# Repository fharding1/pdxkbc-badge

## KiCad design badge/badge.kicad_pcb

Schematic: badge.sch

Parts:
D1, D2, D3, D4, D5, D6: D; D_SOD123_axial
K1, K2, K3, K4, K5, K6: KEYSW; Mx_Alps_100
U1: ProMicro; SPARKFUN_PRO_MICRO

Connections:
/col0: K1.1, K2.1, K3.1, U1.5
/col1: K4.1, K5.1, K6.1, U1.10
/row0: D1.1 (K), D4.1 (K), U1.17
/row1: D2.1 (K), D5.1 (K), U1.13
/row2: D3.1 (K), D6.1 (K), U1.20
GND: U1.3, U1.4, U1.23
unnamed: D1.2 (A), K1.2
unnamed: D2.2 (A), K2.2
unnamed: D3.2 (A), K3.2
unnamed: D4.2 (A), K4.2
unnamed: D5.2 (A), K5.2
unnamed: D6.2 (A), K6.2

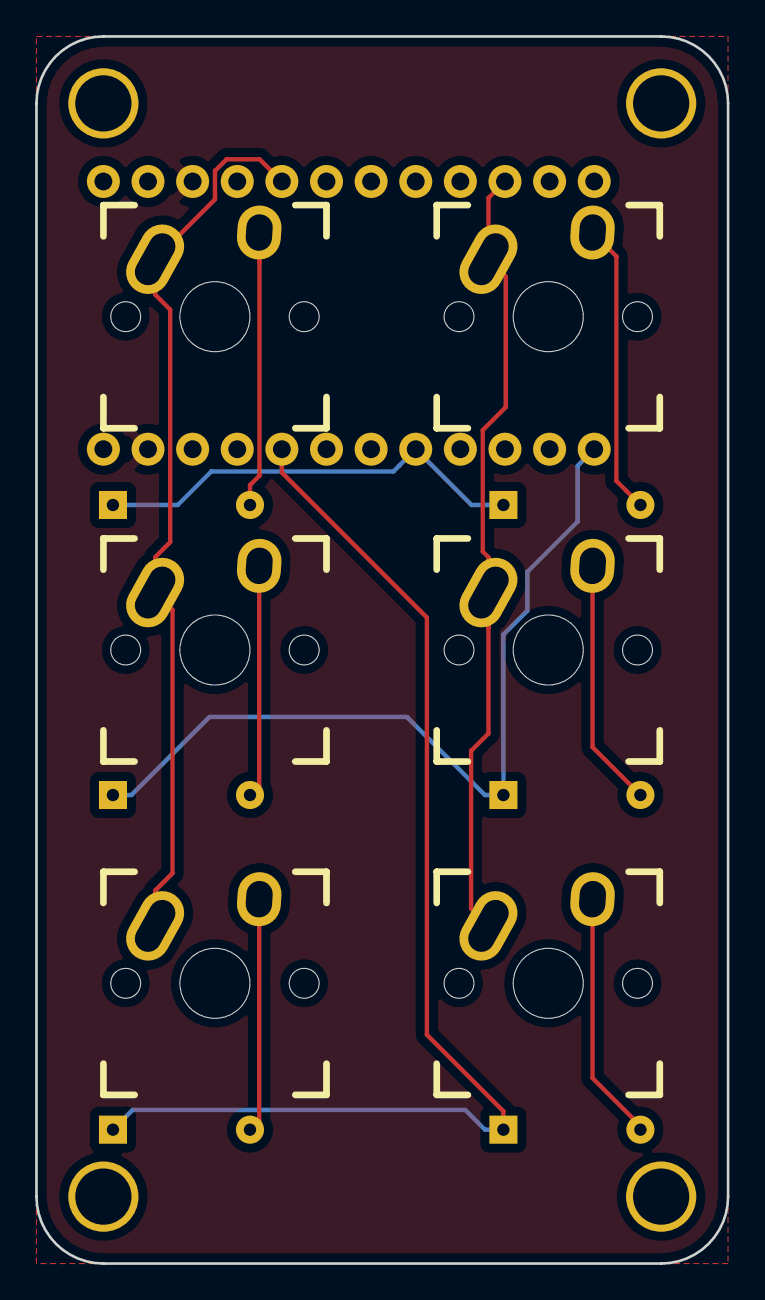
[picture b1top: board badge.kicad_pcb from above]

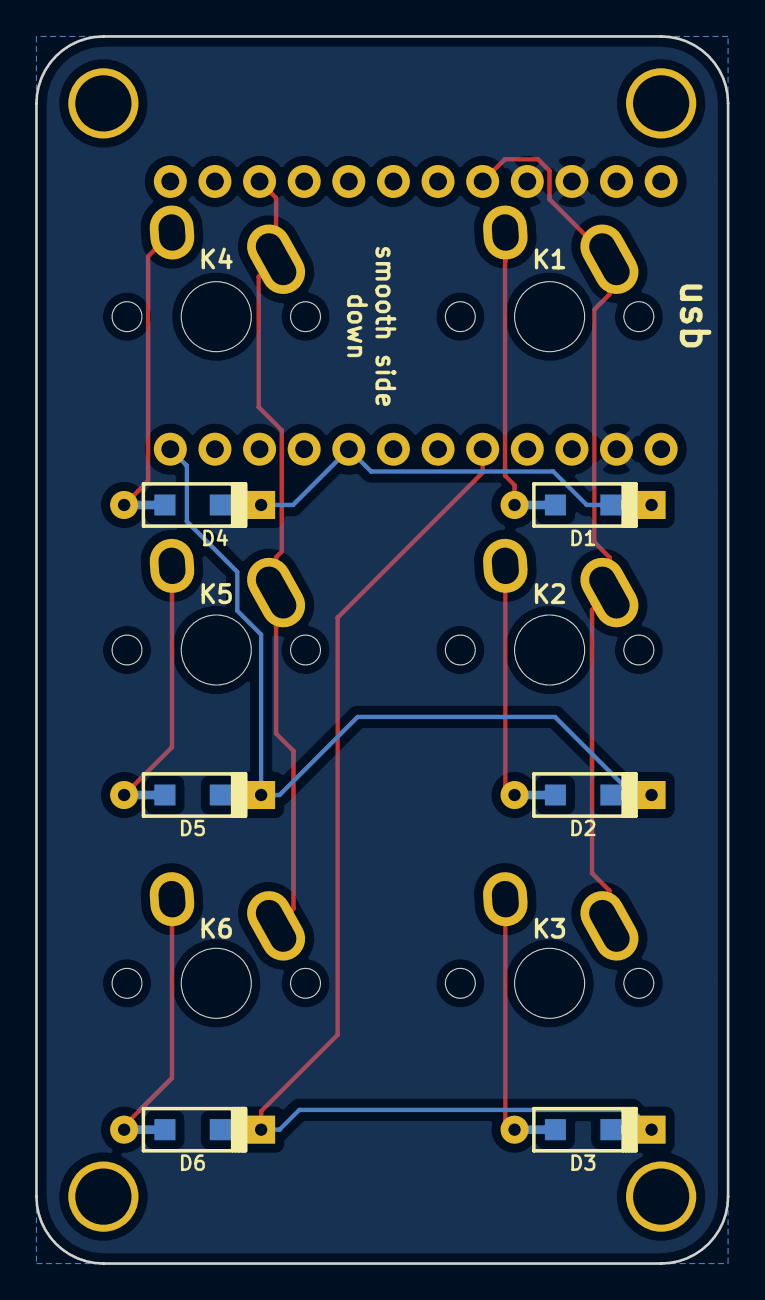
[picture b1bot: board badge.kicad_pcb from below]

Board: 2 copper layers, 39.4 x 69.8 mm, 17 parts (7 on the bottom side), 12 nets.

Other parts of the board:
HOLE_M3, HOLE_M3#2, HOLE_M3#3, HOLE_M3#4: VAL**; HOLE_M3

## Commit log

2019-05-12 Initial
2019-05-12 Move logos around a bit
2019-05-12 Make rose smaller so it doesn't expose nodes
2019-05-12 Cleanup routing, position logos relatively
2019-05-12 Make name silkscreen (not exposed cu), in the corner, and smaller
    Vain af
2019-05-13 Use different pro micro pins for easier routing
2019-05-22 Use SparkFun library, the keebs pro micro is wrong
2019-06-01 2x3 layout and case
2020-03-19 Add CC-BY-SA license
